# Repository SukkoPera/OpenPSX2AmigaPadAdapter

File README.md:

# OpenPSX2AmigaPadAdapter
OpenPSX2AmigaPadAdapter is an Open Hardware adapter that allows using a Sony PlayStation controller on Commodore computers, including the Commodore 64, Amiga and CD<sup>32</sup>.

## Summary
The Commodore Amiga CD<sup>32</sup> came with cumbersome and fragile controllers, most of which did not survive the challenge of time. While many third-party replacements have surfaced in the meantime, most of them are not as solid and comfortable as the ubiquitous Sony PlayStation controllers. These have more than enough buttons, are cheap and most people are familiar with them, as the same basic design has been around for nearly 25 years. This means they would be a very good replacement, if they just didn't use a different connector and communication protocol.

OpenPSX2AmigaPadAdapter is a simple [Arduino](https://www.arduino.cc)-based board that adapts the connector and translates the protocol, allowing the use of many PlayStation controllers on Commodore computers. It can either behave as a simple 1/2-button Atari-style joystick or as a full-fledged 7-button CD<sup>32</sup> gamepad. It can also appear as an Amiga mouse.

## Operating Modes
The adapter has two leds:
- LD1 lights up steadily when a supported controller is plugged in. It blinks when no controller - or an unsupported one - is connected.
- LD2 indicates the current operating mode, to be interpreted as follows.

### Two-Button Joystick Mode
When the adapter is powered on, it defaults to Atari-style Two-Button Mode, which is indicated by LD2 being off.

This mode has been throughly tested on several Amiga models, but it **should** work wherever an Atari-style joystick is supported, including the Commodore VIC-20, Commodore 16 (through an [adapter](https://github.com/SukkoPera/OpenC16JoyAdapter)), Commodore 64, etc. See [below](#computers-and-consoles) for a compatibility table.

While in this mode, the adapter supports different button mappings, which have been carefully designed and tailored to different game genres. The mappings can be switched by pressing <kbd>Select</kbd> in combination with other buttons. LD2 will blink quickly a few times to indicate what mapping has been activated.

#### Standard Mapping: <kbd>Select</kbd> + <kbd>&square;</kbd>
Standard Mapping is the simplest mapping possible: both the D-Pad and Left Analog work as direction buttons. <kbd>&square;</kbd> is <kbd>B1</kbd> and <kbd>&cross;</kbd> is <kbd>B2</kbd>. This is the default mapping as it should be usable just about in every game out there. It might not be the most natural these days, but it's the way the game was meant to be played by the developers, thus it should never fail you.

Note that very few games were originally made to take advantage of two buttons, as even fewer controllers had that many (!) those days. [Here is a list](http://eab.abime.net/showthread.php?t=57540) of Amiga games that somehow support two buttons, if it can be any useful.

LD2 will blink once when this mapping is activated.

#### Racing Mapping 1: <kbd>Select</kbd> + <kbd>&triangle;</kbd>
Racing Mapping 1 is useful for all those racing games that use <kbd>&uarr;</kbd> to accelerate and <kbd>&darr;</kbd> to brake. These have been mapped to <kbd>&square;</kbd> and <kbd>&cross;</kbd>, respectively, which should make them much more natural to play. When accelerating and braking at the same time, braking wins. Left Analog can be used to steer, but its vertical axis is ignored, to avoid accidental accelerating/braking. The D-Pad is fully functional and is handy when moving through menus. <kbd>B1</kbd> and <kbd>B2</kbd> can be found on <kbd>&triangle;</kbd> and <kbd>&cir;</kbd>.

This mode is probably best suited to games that do not involve shifting gears, as downshifting is usually performed through <kbd>&darr;</kbd> + <kbd>B1</kbd> which is pretty hard to achieve (<kbd>&triangle;</kbd> + <kbd>&cross;</kbd>).

LD2 will blink twice when this mapping is activated.

#### Racing Mapping 2: <kbd>Select</kbd> + <kbd>&cir;</kbd>
Racing Mapping 2 is an alternative mapping for racing games that was inspired by GTA V. It lets you use <kbd>R2</kbd> (or <kbd>R1</kbd>) to accelerate and <kbd>L2</kbd> (or <kbd>L1</kbd>) to brake (which means they map to <kbd>&uarr;</kbd> and <kbd>&darr;</kbd>, respectively). <kbd>B1</kbd> is mapped to its natural <kbd>&square;</kbd> position. Steering and the D-Pad work as in Racing Mode 1.

Accidentally, this control scheme was found out to be very comfortable with games that use <kbd>B1</kbd> to accelerate and <kbd>&uarr;</kbd> and <kbd>&darr;</kbd> to shift gears. Since <kbd>&darr;</kbd> is probably used for braking as well, it has also been mapped to <kbd>&cross;</kbd>, while <kbd>B2</kbd> has been moved to <kbd>&triangle;</kbd>.

LD2 will blink three times when this mapping is activated.

#### Platform Mapping: <kbd>Select</kbd> + <kbd>&cross;</kbd>
Platform Mapping is very similar to Standard Mapping, it just makes jumping way easier on a joypad and more natural to all the Mario players out there, by replicating <kbd>&uarr;</kbd> on <kbd>&cross;</kbd>. Consequently, <kbd>B2</kbd> has been moved to <kbd>&triangle;</kbd>.

LD2 will blink four times when this mapping is activated.

#### Custom Mappings: <kbd>Select</kbd> + <kbd>R1</kbd>/<kbd>R2</kbd>/<kbd>L1</kbd>/<kbd>L2</kbd>
What if the built-in mappings are not enough? OpenPSX2AmigaPadAdapter allows you to make your own! And you can have up to four different ones, which are stored internally so that they can be recalled at any time. By default they behave similarly to the Standard Mapping, but they can be customized so that any button produces either the press of a single button or even of a button combo!

The programming procedure is as follows:

1. Press and hold <kbd>Select</kbd>, then press and hold one of <kbd>R1</kbd>/<kbd>R2</kbd>/<kbd>L1</kbd>/<kbd>L2</kbd> until LD2 starts blinking, finally release both buttons. You are now in Programming Mode.
2. Press the button you want to configure. LD2 will flash quickly a few times.
3. Press and hold the single button or button combo you want to be assigned to the button you pressed before. At this stage the D-Pad directions have their obvious meaning, while <kbd>&square;</kbd> represents <kbd>B1</kbd> and <kbd>&cross;</kbd> represents <kbd>B2</kbd>. LD2 will again flash quickly a few times.
4. Release the button or combo you were holding.
5. Repeat steps 2-4 for every button you want to customize.
6. When you are done, press <kbd>Select</kbd> to store the mapping and leave Programming Mode. LD2 will stop blinking and you will be back to Two-Button Joystick Mode.

Note that a mapping you have just programmed is not activated automatically, so you will have to press <kbd>Select</kbd> and one of <kbd>R1</kbd>/<kbd>R2</kbd>/<kbd>L1</kbd>/<kbd>L2</kbd> (and release them quickly) to switch to it.

The Custom Mappings **cannot** be configured so that <kbd>&darr;</kbd> overrides <kbd>&uarr;</kbd> or so that the vertical axis of Left Analog is ignored, still they might be useful here and there. For instance, having <kbd>B1</kbd> + <kbd>&uarr;</kbd> on <kbd>&cross;</kbd> and <kbd>B1</kbd> + <kbd>&darr;</kbd> on <kbd>&triangle;</kbd> makes the Amiga version of *Golden Axe* much more playable.

#### Commodore 64 Mode
Button 2 on Commodore 64 usually behaves in the opposite way at the electrical level, with respect to the other buttons. So a tweak can be enabled to invert the behaviour of button 2, use it if you find that your game of choice always sees it pressed or if it triggers on release rather than on press.

Just hold <kbd>Select</kbd> and press <kbd>Start</kbd> briefly. LD2 will flash once when this tweak is enabled and twice when it is disabled.

### Mouse Mode
Whenever the right analog stick is moved, the adapter switches to Amiga Mouse Mode. In this mode, the right stick emulates the movements of a mouse. Movement speed is somewhat proportional to how far the stick is moved.

This mode can be useful as an emergency mouse, and it will be particularly handy if you have the adapter connected to port 1 of an Amiga computer and you need to use a mouse for short while (maybe to do some settings in a cracktro). Instead of unplugging the adapter, plugging in a mouse, and then the adapter again, you can take advantage of this feature.

Mouse mode is indicated by LD2 blinking. Press any direction on the D-Pad to go back to Joystick or CD32 Mode.

### CD<sup>32</sup> Controller Mode
When the adapter is connected to a CD<sup>32</sup> console, it will automatically switch into this mode, which will emulate all 7 buttons of the original CD<sup>32</sup> controller. LD2 will light up steadily.

By default, buttons are mapped as follows:
- <kbd>&square;</kbd>: Red
- <kbd>&cross;</kbd>: Blue
- <kbd>&cir;</kbd>: Yellow
- <kbd>&triangle;</kbd>: Green
- <kbd>L1</kbd>/<kbd>L2</kbd>/<kbd>L3</kbd>: L
- <kbd>R1</kbd>/<kbd>R2</kbd>/<kbd>R3</kbd>: R
- <kbd>Start</kbd>: Start/Pause

If you press <kbd>Select</kbd>, the 4 main buttons get "rotated":
- <kbd>&cross;</kbd>: Red
- <kbd>&cir;</kbd>: Blue
- <kbd>&triangle;</kbd>: Yellow
- <kbd>&square;</kbd>: Green

Both the D-Pad and Left Analog always work as direction buttons.

## Components and Assembly
The board is basically a customized Arduino Uno, this means it was designed to work with an ATmega328P microcontroller, but you can also use ATmega88/A/P/PA or ATmega168/P microcontrollers, as they are pin-compatible and slightly cheaper. The A/P/PA suffixes usually identify somewhat minor chip revisions, the board should work with all of them. If you can, use P or PA versions, which consume less power. Note that at the moment the firmware uses 99% of the flash space available on an ATmega88 and any possible future improvements and/or new features are likely to overflow that, so you'd better use an ATmega168 at least.

A noteworthy exception to this rule is the ATmega328P**B**, which is NOT 100% pin-compatible with the 328P. Nevertheless, it MIGHT just work as well. It might also destroy whatever you connect the adapter to, so do it **at your own risk**.

You are recommended to solder the microcontroller first. The TQFP-32 package is easier to solder than it looks, watch some videos on YouTube and develop your own technique. Just make sure to orient it correctly.

Solder the oscillator then. You can either use a through-hole crystal with its caps (these will depend on the crystal, but usually 18-22pF are a good bet) or a 3-pin resonator. Whichever you choose, it shall have a frequency of 16 MHz. If you choose the crystal, you might want to put some insulation tape under it to avoid it touching the pads for the resonator.

Solder all the remaining parts in the order you prefer, just keep the controller connectors last.

Note that the PlayStation controller is powered at 3.3V and the interface signals use the same voltage. Due to the particular circuit used for level shifting (the microcontroller works at 5V), the MOSFETs [should really be BSS138](https://electronics.stackexchange.com/questions/367052/replace-bss138-with-ao3400a-in-level-shifter-circuit).

The PlayStation controller connector can be found from many Chinese sellers as a spare part. Get one with 90° pins, otherwise the adapter will be pretty awkward to use. The pins will be pretty short, but you should manage to solder it in place. Make sure it sits level on the board, otherwise it might not fit in the [3D-printable case](#enclosure), which you are recommended to use in order to make the adapter more mechanically solid. In alternative, some hot glue behind the connector (where the pins are) seems to do the same job, but it won't look as pretty.

**Hint:** If you don't have the PCB, you can build a full adapter with an Arduino Uno/Nano/Whatever board. This is not supported though, so you are on your own, but all the information you need is in the schematics or in the firmware code :).

## Firmware
Before you can use the adapter, you will need to load some firmware (i.e.: an Arduino sketch) on it. This can be found under the [firmware](https://github.com/SukkoPera/OpenPSX2AmigaPadAdapter/tree/master/firmware) directory, along with instructions.

## Compatibility
### Computers and Consoles
|System                           |Compatible             |Notes                                                                                                                                                                                |
|---------------------------------|-----------------------|-------------------------------------------------------------------------------------------------------------------------------------------------------------------------------------|
|Commodore Amiga (All models)     |    |Tested on A500+ and A1200 (1.D3), it is expected to be compatible with all models in both 2- and 7-button Joystick modes and in Mouse mode.                                          |
|Commodore Amiga CD<sup>32</sup>  |    |Both 2- and 7-button Joystick modes and Mouse mode. Games not using `lowlevel.library` might be a bit of hit-and-miss, please report any misbehaviours.                              |
|Commodore CDTV                   ||**Not tested yet**, but expected to work in 2-button Joystick mode and Mouse mode through a connector adapter.                                                                       |
|Commodore 64                     |    |Tested in 2-button Joystick mode, but second button untested. Mouse mode might damage CIA chips though, be careful not to turn it on!                                                |
|Commodore 16                     ||**Not tested yet**, but expected to work in 2-button Joystick mode through [OpenC16JoyAdapter](https://github.com/SukkoPera/OpenC16JoyAdapter). C16 only supports Button 1 though.   |
|Commodore VIC-20                 ||**Not tested yet**, but expected to work in 2-button Joystick mode. Be careful with Mouse mode.                                                                                      |
|Sega Master System               |      |Would probably work in 2-button Joystick mode if power was routed from pin 5 on the SMS controller port to pin 7 of the adapter.                                                     |
|Sega Mega Drive/Genesis          |      |Would probably work as an SMS controller with the same mod as above. Some more pin rerouting AND a custom firmware could make it appear as a Mega Drive 6-button controller.         |
|MSX                              |      |Would probably work in 2-button Joystick mode by swapping a few pins on the controller port.                                                                                         |

### Controllers
The latest versions of the OpenPSX2AmigaPadAdapter firmware use [PsxNewLib](https://github.com/SukkoPera/PsxNewLib) to read the PlayStation controller. This makes it compatible with (almost) all controllers.

Please refer to the [PsxNewLib Compatibility List](https://github.com/SukkoPera/PsxNewLib#compatibility-list) for details.

## Current Consumption
Following are the results of some rough measurements:
- An ATmega88PA-based OpenPSX2AmigaPadAdapter with an original Sony Dual Shock/Dual Shock 2 controller connected draws about 20 mA.
- Consumption rises to 25 mA with the dongle of my EastVita wireless controller, when the controller is connected. It peaks to 35 mA while it is searching for the controller.
- Using an ATmega328P bumps all consumptions by 5 mA.

This means that the current absorbed by the adapter is "reasonable" and that it should be safe to use in all cases. It is well below the 100 mA maximum available from any Amiga controller ports, for instance.

## Enclosure
Three different 3D-printable enclosures are currently available for this board:
- The [first](https://github.com/SukkoPera/OpenPSX2AmigaPadAdapter/tree/master/enclosure) one was kindly contributed by Petros Kokotis and needs screws for assembly.
- A [second one](https://www.thingiverse.com/thing:4620027) was designed by Lemaru and uses a snap-in design. It also has holes for the LEDs.
- [Another one](https://github.com/SukkoPera/OpenPSX2AmigaPadAdapter/tree/master/enclosure/cd32) was made by Gary Ogden and is better suited for use with the CD<sup>32</sup>, as it has some kind of bottom support.

My gratitude goes to all the three guys for their great work and support!

### Releases
If you want to get this board produced, you are recommended to get [the latest release](https://github.com/SukkoPera/OpenPSX2AmigaPadAdapter/releases) rather than the current git version, as the latter might be under development and is not guaranteed to be working.

Every release is accompanied by its Bill Of Materials (BOM) file and any relevant notes about it, which you are recommended to read carefully.

## License
The OpenPSX2AmigaPadAdapter documentation, including the design itself, is copyright &copy; SukkoPera 2019-2020.

OpenPSX2AmigaPadAdapter is Open Hardware licensed under the [CERN OHL v. 1.2](http://ohwr.org/cernohl).

You may redistribute and modify this documentation under the terms of the CERN OHL v.1.2. This documentation is distributed *as is* and WITHOUT ANY EXPRESS OR IMPLIED WARRANTIES whatsoever with respect to its functionality, operability or use, including, without limitation, any implied warranties OF MERCHANTABILITY, SATISFACTORY QUALITY, FITNESS FOR A PARTICULAR PURPOSE or infringement. We expressly disclaim any liability whatsoever for any direct, indirect, consequential, incidental or special damages, including, without limitation, lost revenues, lost profits, losses resulting from business interruption or loss of data, regardless of the form of action or legal theory under which the liability may be asserted, even if advised of the possibility or likelihood of such damages.

A copy of the full license is included in file [LICENSE.pdf](LICENSE.pdf), please refer to it for applicable conditions. In order to properly deal with its terms, please see file [LICENSE_HOWTO.pdf](LICENSE_HOWTO.pdf).

The contact points for information about manufactured Products (see section 4.2) are listed in file [PRODUCT.md](PRODUCT.md).

Any modifications made by Licensees (see section 3.4.b) shall be recorded in file [CHANGES.md](CHANGES.md).

The Documentation Location of the original project is https://github.com/SukkoPera/OpenPSX2AmigaPadAdapter/.

## Support the Project
Since the project is open you are free to get the PCBs made by your preferred manufacturer, however in case you want to support the development, you can order them from PCBWay through this link:

You get my gratitude and cheap, professionally-made and good quality PCBs, I get some credit that will help with this and [other projects](https://www.pcbway.com/project/member/shareproject/?bmbid=41100). You won't even have to worry about the various PCB options, it's all pre-configured for you!

Also, if you still have to register to that site, [you can use this link](https://www.pcbway.com/setinvite.aspx?inviteid=41100) to get some bonus initial credit (and yield me some more).

Again, if you want to use another manufacturer, feel free to, don't feel obligated :). But then you can buy me a coffee if you want:

### Get Help
If you need help or have questions, you can join [the official Telegram group](https://t.me/joinchat/HUHdWBC9J9JnYIrvTYfZmg).

### Thanks
- Gerd Kautzmann for information about the [CD32 controller protocol](http://gerdkautzmann.de/cd32gamepad/cd32gamepad.html)
- CuriousInventor for informtation about the [PlayStation controller protocol](http://store.curiousinventor.com/guides/PS2)
- majinga/screwbreaker for testing and bugfixes
- Petros Kokotis, Lemaru and Gary Ogden for the 3D-printable enclosures
- Sarang Dumbre for the [3D model of the PlayStation connector](https://grabcad.com/library/ps-connector-female-1)

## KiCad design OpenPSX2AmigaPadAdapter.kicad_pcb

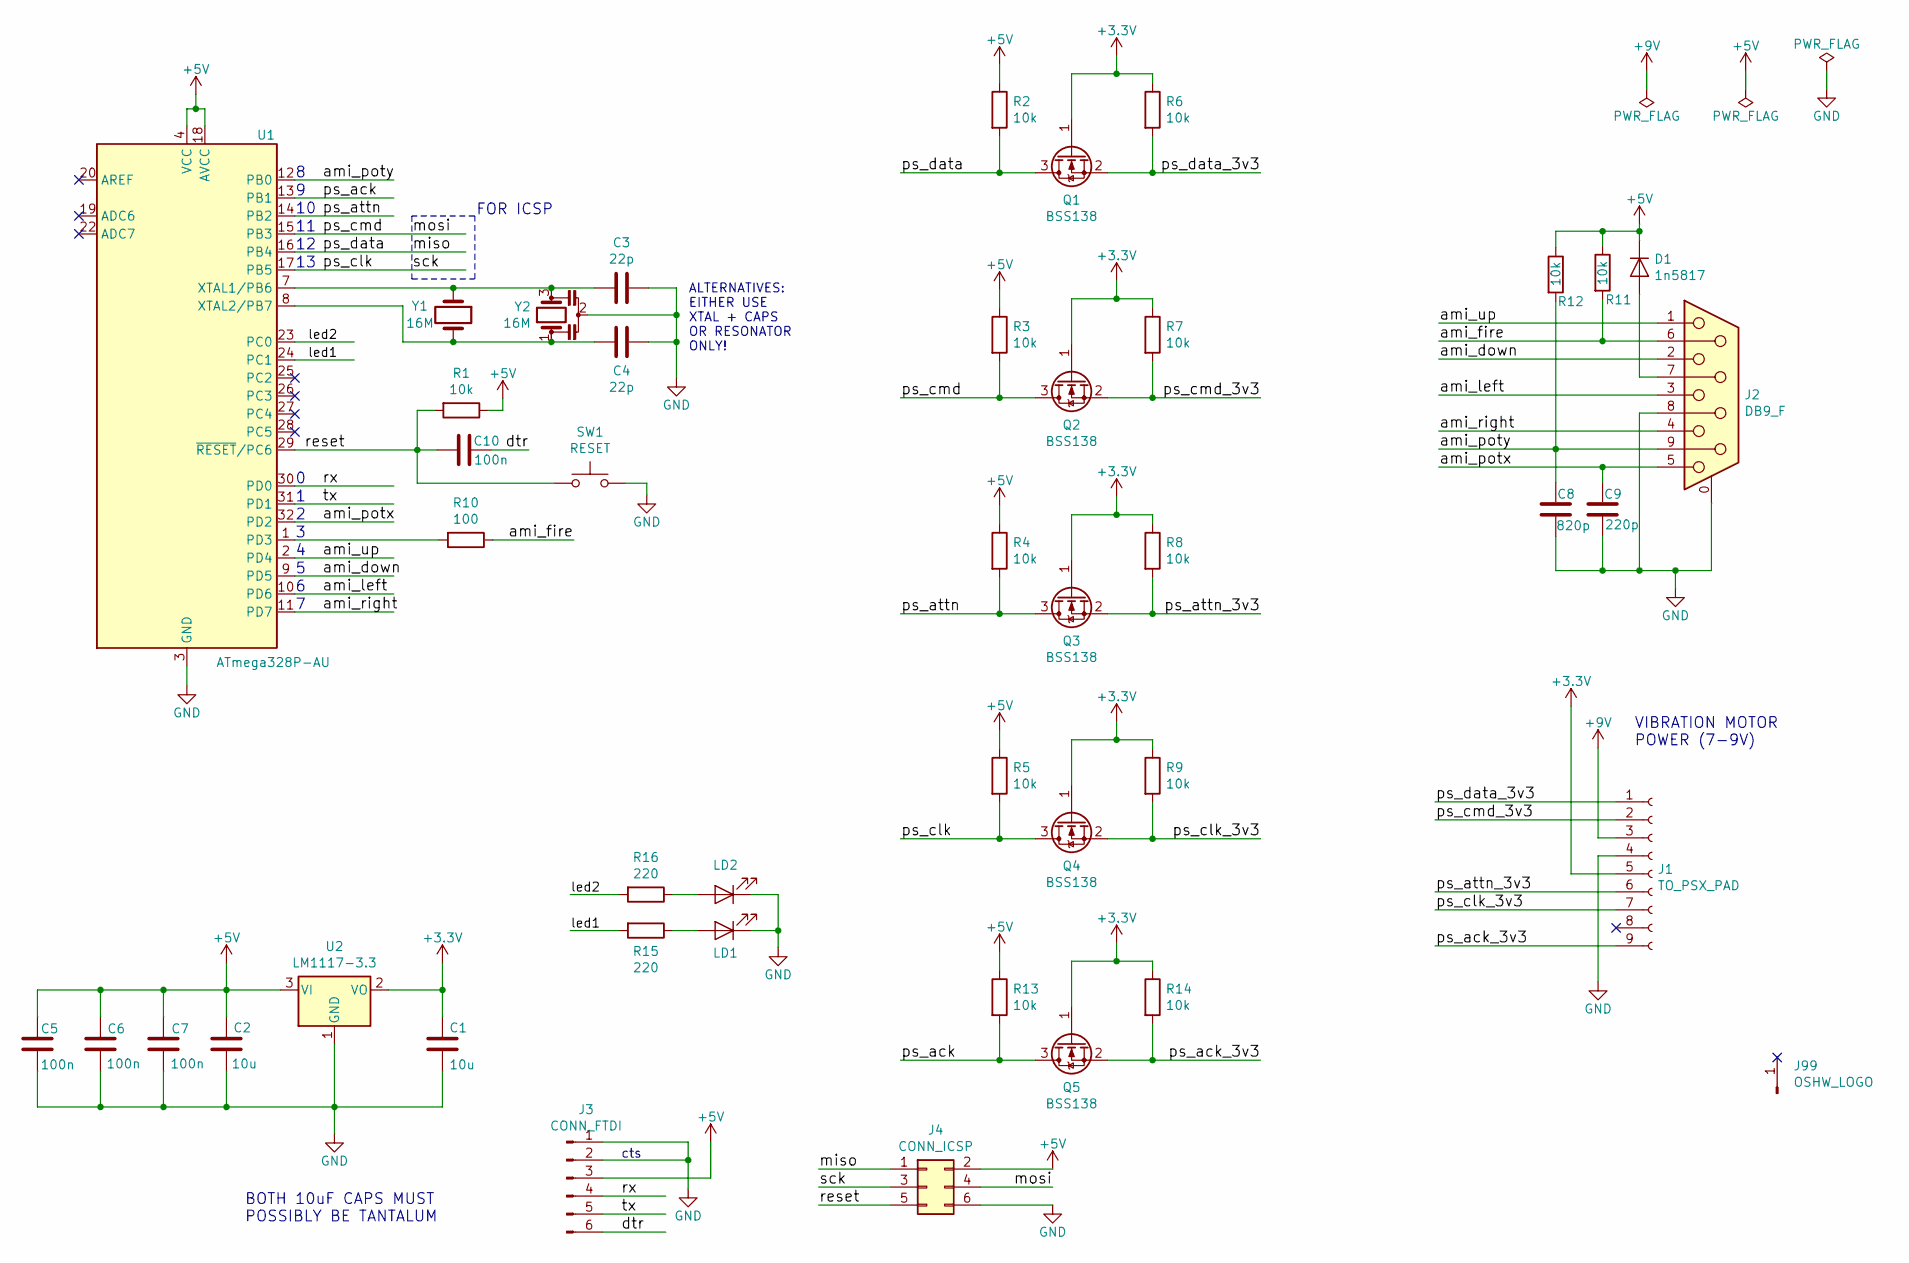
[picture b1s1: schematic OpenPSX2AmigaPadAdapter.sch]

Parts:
C1, C2: 10u; C_1206_3216Metric_Pad1.42x1.75mm_HandSolder
C3, C4: 22p; C_0805_2012Metric_Pad1.15x1.40mm_HandSolder
C5, C6, C7, C10: 100n; C_0805_2012Metric_Pad1.15x1.40mm_HandSolder
C8: 820p; C_0805_2012Metric_Pad1.15x1.40mm_HandSolder
C9: 220p; C_0805_2012Metric_Pad1.15x1.40mm_HandSolder
D1: 1n5817; D_SMA
J1: TO_PSX_PAD; PSX_Pad_Connector
J2: DB9_F; DB_9F
J3: CONN_FTDI; PinHeader_1x06_P2.54mm_Vertical
J4: CONN_ICSP; PinHeader_2x03_P2.54mm_Vertical
J99: OSHW_LOGO; OSHW-Logo_5.7x6mm_Copper
LD1, LD2: LED; LED_0805_2012Metric_Pad1.15x1.40mm_HandSolder
Q1, Q2, Q3, Q4, Q5: BSS138; SOT-23_Handsoldering
R1, R2, R3, R4, R5, R6, R7, R8, R9, R11, R12, R13, R14: 10k; R_0805_2012Metric_Pad1.15x1.40mm_HandSolder
R10: 100; R_0805_2012Metric_Pad1.15x1.40mm_HandSolder
R15, R16: 220; R_0805_2012Metric_Pad1.15x1.40mm_HandSolder
SW1: RESET
U1: ATmega328P-AU; TQFP-32_7x7mm_P0.8mm
U2: LM1117-3.3; SOT-223-3_TabPin2
Y1: 16M; Crystal_HC49-U_Vertical
Y2: 16M; Resonator_SMD_muRata_CSTxExxV

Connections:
+3V3: C1.2, J1.5, Q1.1 (G), Q2.1 (G), Q3.1 (G), Q4.1 (G), Q5.1 (G), R6.1, R7.1, R8.1, R9.1, R14.1, U2.2 (VO)
+5V: C2.2, C5.2, C6.2, C7.2, D1.1 (K), J3.3, J4.2, R1.1, R2.1, R3.1, R4.1, R5.1, R11.1, R12.1, R13.1, U1.4 (VCC), U1.6 (VCC), U1.18 (AVCC), U2.3 (VI)
/ami_down: J2.2, U1.9 (PD5)
/ami_fire: J2.6, R10.1, R11.2
/ami_left: J2.3, U1.10 (PD6)
/ami_potx: C9.1, J2.5, U1.32 (PD2)
/ami_poty: C8.1, J2.9, R12.2, U1.12 (PB0)
/ami_right: J2.4, U1.11 (PD7)
/ami_up: J2.1, U1.2 (PD4)
/dtr: C10.1, J3.6
/led1: R15.2, U1.24 (PC1)
/led2: R16.2, U1.23 (PC0)
/miso: J4.1, Q1.3 (D), R2.2, U1.16 (PB4)
/mosi: J4.4, Q2.3 (D), R3.2, U1.15 (PB3)
/ps_ack: Q5.3 (D), R13.2, U1.13 (PB1)
/ps_ack_3v3: J1.9, Q5.2 (S), R14.2
/ps_attn: Q3.3 (D), R4.2, U1.14 (PB2)
/ps_attn_3v3: J1.6, Q3.2 (S), R8.2
/ps_clk: J4.3, Q4.3 (D), R5.2, U1.17 (PB5)
/ps_clk_3v3: J1.7, Q4.2 (S), R9.2
/ps_cmd_3v3: J1.2, Q2.2 (S), R7.2
/ps_data_3v3: J1.1, Q1.2 (S), R6.2
/reset: C10.2, J4.5, R1.2, SW1.1, U1.29 (~RESET~/PC6)
/rx: J3.4, U1.30 (PD0)
/tx: J3.5, U1.31 (PD1)
GND: C1.1, C2.1, C3.1, C4.1, C5.1, C6.1, C7.1, C8.2, C9.2, J1.4, J2.0 (PAD), J2.8, J3.1, J3.2, J4.6, LD1.1 (K), LD2.1 (K), SW1.2, U1.3 (GND), U1.5 (GND), U1.21 (GND), U2.1 (GND), Y2.2
unnamed: C3.2, U1.7 (XTAL1/PB6), Y1.1, Y2.3
unnamed: C4.2, U1.8 (XTAL2/PB7), Y1.2, Y2.1
unnamed: D1.2 (A), J2.7
unnamed: LD1.2 (A), R15.1
unnamed: LD2.2 (A), R16.1
unnamed: R10.2, U1.1 (PD3)

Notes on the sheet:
VIBRATION MOTOR POWER (7-9V)
BOTH 10uF CAPS MUST POSSIBLY BE TANTALUM
FOR ICSP
ALTERNATIVES: EITHER USE XTAL + CAPS OR RESONATOR ONLY!
cts

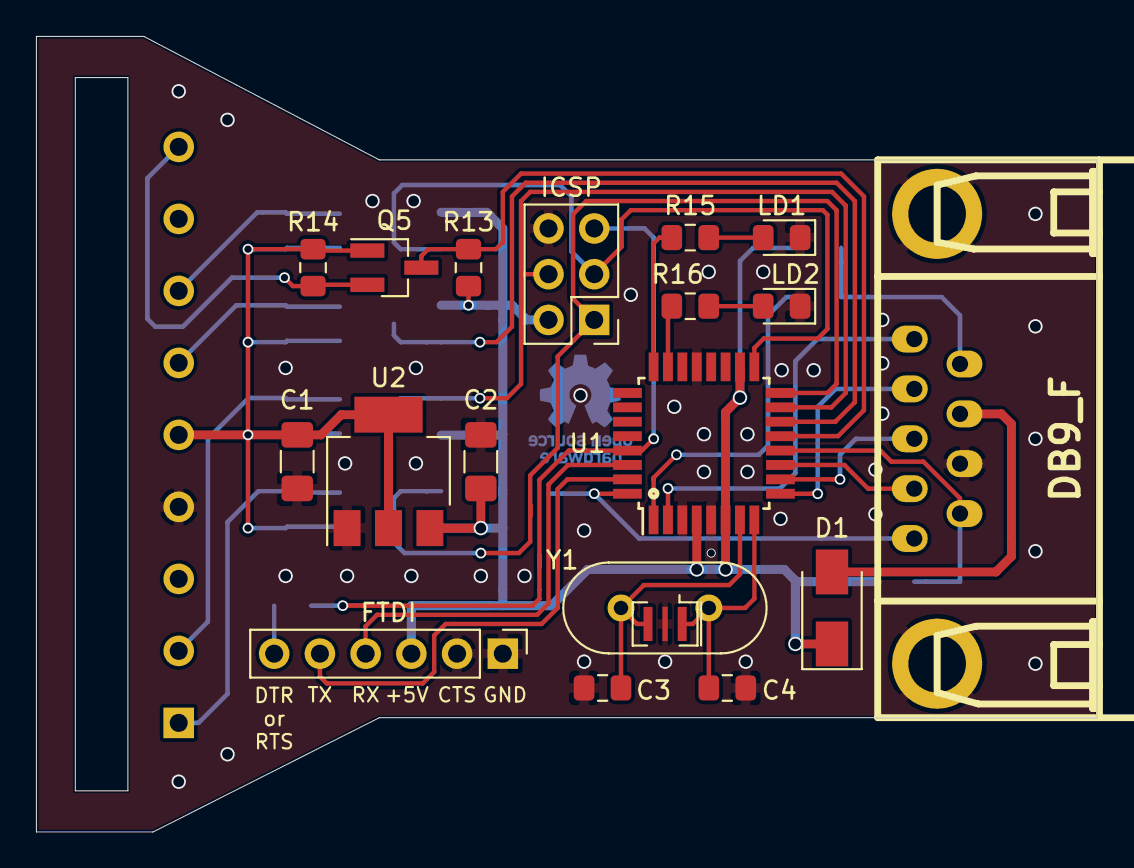
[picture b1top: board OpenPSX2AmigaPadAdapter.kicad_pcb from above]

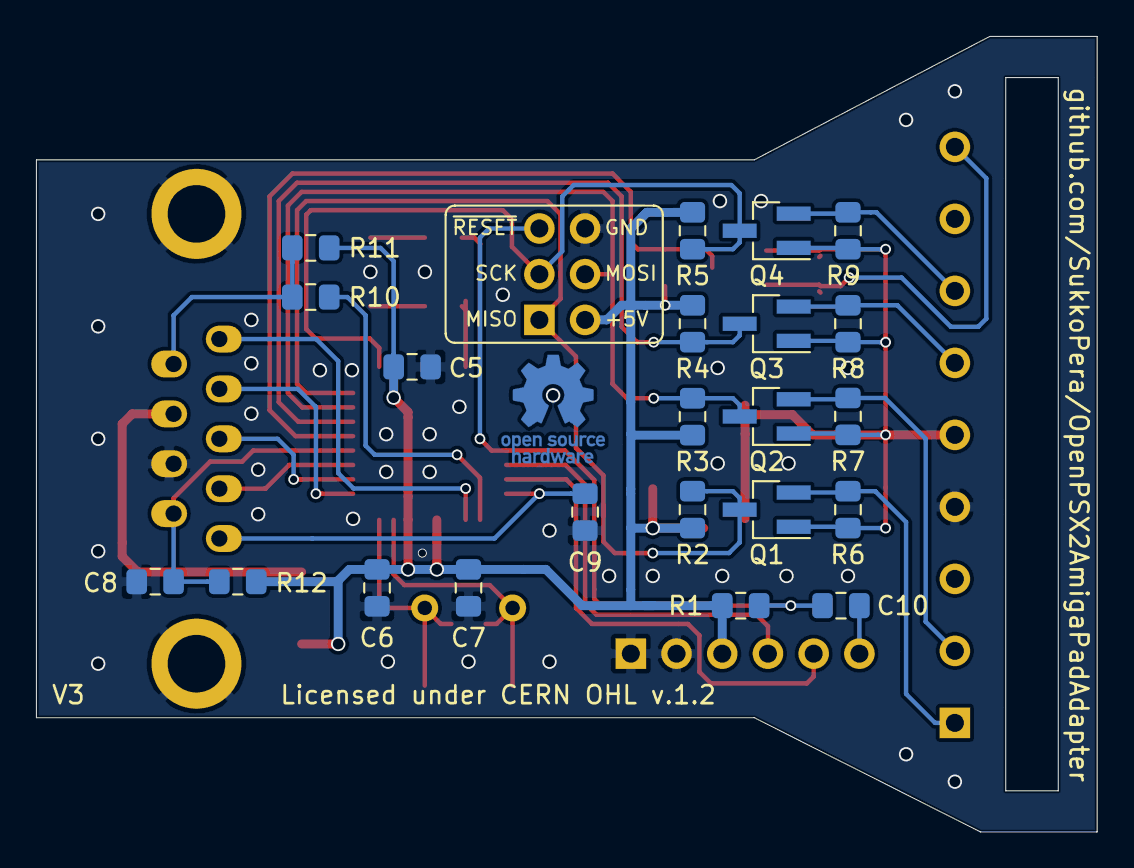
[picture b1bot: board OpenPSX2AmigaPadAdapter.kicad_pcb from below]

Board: 2 copper layers, 58.9 x 44.2 mm, 43 parts (23 on the bottom side), 32 nets.

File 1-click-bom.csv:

References,Qty,Description,Manufacturer,MPN,Manufacturer,MPN,Manufacturer,MPN,Manufacturer,MPN,Manufacturer,MPN,LCSC,Digikey,Mouser,RS,Newark,Farnell
J1,1,"1x09, 2.54mm pitch pin header",Molex,74099-0009,,,,,,,,,,23-0740990009-ND,538740990009,,,3036258
"C2, C1",2,10uF 1206,TDK,C3216JB1E106K160AB,AVX,TAJA106K016RNJ,Samsung Electro-Mechanics,CL31B106KAHNNNE,,,,,C7171,478-1655-1-ND,581TAJA106K016R,1354012,,1432339
"C7, C6, C5, C10",4,100nF 0805,Yageo,CC0805KRX7R9BB104,Murata,GCM21BR71H104KA37L,Murata,GRM21BR71H104KA01L,Guangdong Fenghua Advanced Tech,0805B104K500NT,,,C161260,311-1140-1-ND,603CC805KRX7R9BB104,6698842,,3019949
"C3, C4",2,22pF 0805,KEMET,C0805C220J5GAC,CCTC,TCC0805COG220J500BT,KEMET,C0805C220J5GACTU,,,,,C376875,399-1113-1-ND,80C0805C220J5GAC,2644258P,,1414678
"LD2, LD1",2,led 0805,Everlight,17-21/GHC-XS1T2M/3T,Lumex,SML-LXT0805GW-TR,Everlight,17-21SYGC/S530-E3/TR8,Rohm,SML-210VTT86,,,C63855,67-1553-6-ND,696SMLLXT0805GW,7007893,,2062259
"Q1, Q2, Q3, Q4",4,,MCC,BSS138-TP,,,,,,,,,C435876,BSS138-TPMSCT-ND,833BSS138TP,,,
"R1, R2, R3, R4, R5, R6, R7, R8, R9, R13, R12, R11",12,10k 0805,Vishay,CRCW080510K0FKEA,Panasonic,ERJ-6ENF1002V,Rohm,MCR10EZPJ103,Yageo,RC0805FR-0710KL,Guangdong Fenghua Advanced Tech,RS-05K103JT,C115295,311-10.0KCRCT-ND,603RC0805FR0710KL,1694499,,9237755
R10,1,100 ohm 0805,Vishay,CRCW0805100RFKEA,Panasonic,ERJ-6ENF1000V,Yageo,RC0805FR-07100RL,Guangdong Fenghua Advanced Tech,RS-05K101JT,,,C193990,311-100CRDKR-ND,603RC0805FR07100RL,7326034,,2459312
"R15, R14",2,220 ohm 0805,Yageo,AC0805JR-07220RL,LIZ Elec,CR0805F82200G,Panasonic,ERJ6ENF2200V,,,,,C413269,P220CCT-ND,667ERJ6ENF2200V,7326194,,2303479
U1,1,,,ATmega328P-AU,Microchip,ATMEGA328PB-AU,,,,,,,C132230,ATMEGA328PB-AU-ND,556ATMEGA328PBAU,1468928,,2523203
U2,1,LM1117-3.3 SOT-223-3,"Youtai Semiconductor Co., Ltd.",AMS1117-3.3,Texas Instruments,LM1117MPX-3.3/NOPB,,,,,,,C347222,LM1117MPX-3.3/NOPBDKR-ND,926LM1117MPX3.3NOPB,,,3122024
Y1 or Y2,1,Crystal THT HC-49 U 16Mhz,Murata,CSTNE16M0VH3C000R0,,,,,,,,,,490-17951-1-ND,81CSTNE16M0VH3C000R,,,
J3,1,"1x06, 2.54mm pitch, single row",Molex,90120-0126,,,,,,,,,,WM8076-ND,538901200126,6705039,,2313717
J4,1,"2x03, 2.54mm pitch",Molex,90131-0123,,,,,,,,,,WM50035-06-ND,538901310123,6703443,,2381222
J2,1,,TE Connectivity,3-1634584-2,,,,,,,,,C167327,A118456-ND,571316345842,,,8391360
SW1,1,tactile switch smt,Omron,B3S-1000,C&K Components,PTS840 GMP SMTR LFS,,,,,,,,CKN10513DKR-ND,611PTS840GMPSMTR,183701,,177807
D1,1,Diode SMA (DO-214AC) 1n5817,,1n5817,ON Semiconductor,1N5817RLG,,,,,,,C232461,1N5817RLGOSCT-ND,8631N5817RLG,6254972,,2440587
C8,1,820pF 0805,Walsin Technologies,0805B821K500CT,AVX,08055A821JAT2A,Vishay,VJ0805A821JXAAC,,,,,,478-1327-1-ND,77VJ0805A821JXAAC,1353221,,2896735
C9,1,220pF 0805,Fenghua Electronics,0402B221K500NT,Walsin Technologies,0805B221K500,AVX,08051A221JAT2A,KEMET,C0805C221J5GAC,,,,478-1286-1-ND,80C0805C221J5GAC,1351301,,498609

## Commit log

2019-01-01 Minor improvements
2019-06-30 Add cap for ATmega decoupling
2019-06-30 Port to KiCad 5
2019-06-30 Start work on PCB
2019-07-01 Add initial firmware Basically working in CD32 mode only
2019-07-01 This version seems to work pretty well With SysTest, at least. Needs some polishing anyway.
2019-07-02 Add mouse mode
2019-07-02 Begin working on PCB
2019-07-03 Ready?
2019-08-04 Ready for prototype
2019-08-04 Add dimensions
2019-09-10 Use pins as on PCB
2019-09-10 Fully implement button maps and general cleanup
2019-09-10 Avoid useless bit inversions
2019-09-10 Switch to... switch
2019-09-10 Remove register variable attempts These don't seem to be usable in Arduino
2019-09-10 Detach interrupt when switching back from CD32 mode
2019-09-11 Do not accelerate and brake at the same time
2019-09-11 Use better function/struct names
2019-09-11 Fix debug messages & do not crash when Amiga is reset
2019-09-11 Cleanup
2019-09-11 mapJoystick() -> handleJoystick()
2019-09-11 Ready for V2 Added RESET button and lotsa minor adjustments
2019-09-11 Fix dimension
2019-09-11 Use cross to brake when in Racing2, always set pin directions and some clean up
2019-09-12 Handle pad mode better
2019-09-12 Do not disable clock ISR too early
2019-09-12 Tidy up
2019-09-12 Do not set pin directions twice
2019-09-12 Avoid sampling interrupt catching button value being filled in
2019-09-13 Allow controller hotplugging & unplugging
2019-09-13 Add license
2019-09-13 Minor refinements
2019-09-14 Remove unused library
2019-09-14 Override spurious switch to mouse mode on controller disonnection
2019-09-16 Work in progress
2019-09-16 Programmable keys are a reality!
2019-09-16 Disable debug
2019-09-17 Blink when in programming mode
2019-09-19 Move attachInterrupt() to wrapper function
2019-09-19 Starts working with new state machine
2019-09-19 Use button names in debug messages and isolate led handling
2019-09-19 Rename led pin constant
2019-09-19 Add thanks
2019-09-19 Add NO_CONTROLLER state and cosmetic improvements
2019-09-19 Rationalize mouse mode and introduce the NO_CONTROLLER state
2019-09-20 Add footprint for SMD resonator
2019-09-20 Add pull-up resistors on DATA and ACK
2019-09-20 Cosmetic fixes
2019-09-25 Create Doxyfile
2019-09-25 Custom controller configurations are now saved and restored
2019-09-25 Rename enum value
2019-09-25 Allow 4 custom mappings
2019-09-26 Implement factory reset
2019-09-26 Compile fixes
2019-09-27 Some optimizations
2019-09-27 Remove wasMouse stuff
2019-09-28 Allow disabling factory reset (Saves flash for ATmega88)
2019-09-29 Disable debug by default
2019-10-01 Only allow programming of custom mappings
2019-10-01 Save some flash unifying button to index functions
2019-10-08 Slight optimization
2019-10-08 Another small optimization
2019-10-15 Add list of two-button games
2019-10-21 Switch back to joystick mode immediately after LOAD/SHIFT falling edge
2019-10-21 Remove pull-up on ACK. Add on B1/B2 outputs.
2019-10-21 Add capacitor on potx/y as per original CD32 controller
2019-10-21 Update PCB after changes to schematics
2019-10-23 Use fast I/O functions everywhere
2019-10-23 Add/Fix some super-optimizations
2019-10-23 Output buttons sooner
2019-10-23 Update state diagram and pin mapping
2019-10-23 Update pin mapping
2019-10-23 Fix CD32 mode led
2019-10-23 Minor optimizations
2019-10-23 Fix mouse mode
2019-10-23 Some cleanups
2019-10-23 Toggle pins in mouse mode
2019-10-23 Minor fixes
2019-10-25 Add plugin for Saleae Logic Analyzer
2019-10-25 Add submodule for Saleae Logic Analyzer plugin
2019-10-25 Readd submodule
2019-10-25 Do not use {at,de}tachInterrupt() with SUPER_OPTIMIZE
2019-10-28 Avoid switching pin directions during CD32 mode
2019-10-28 Add (optional) instrumentation calls These can be used to measure the time it takes us to react to clock pulses and how long ISRs last.
2019-10-28 Only poll controller every so often (Fixes mouse mode) Note that this required a lot of extra work.
2019-10-28 Make stateEnteredTime local again, and other optimizations Now we fit again on ATmega88's
2019-10-28 Remove cruft
2019-10-28 Keep state in GPIOR2, saves flash and makes us even faster
2019-10-29 Work on documentation
2019-10-29 Fix typo
2019-10-29 Ready for V2 PCB
2019-10-29 Ignore build directories
2019-10-29 Add README and bootloaders
2019-10-29 Fix title
2019-10-29 Fix heading
2019-10-29 Add README
2019-10-29 Do not switch from Mouse to CD32 mode
2019-10-30 Final PCB fixes for V2
2019-10-30 Add note about ArduinoISP
2019-10-30 Update state diagram
2019-10-30 Remove unused factory reset code
2019-10-30 Add C64-style 2nd button. Closes #4.
2019-10-30 Update bootloaders
2019-10-30 Add 328 and 328pb bootloaders
2019-11-03 Init joystick mode correctly after factory reset This is important because some (knockoff) controllers seem to report SELECT pressed at start. This made us start in factory reset mode for a moment, a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
2019-11-05 Fix typos
2019-11-07 Fix configuration clearing
2019-11-08 Add renders
2019-11-09 Add images
2019-11-09 Fix path
2019-11-09 Make maybe icon yellow
2019-11-09 Correct PCBway project link
2019-11-09 Crop renders
2019-11-09 Add 3D model of PSX connector
2019-11-09 Handle SELECT+START properly
2019-11-09 Add command for setting fuses of ATmega328PB
2019-11-09 Use preformatted text
2019-11-09 Use constant for TIMEOUT_PROGRAMMING_MODE
2019-11-09 Buttons -> PsxButtons
2019-11-10 Only map Square and Cross to B1/B2 with normal mapping
2019-11-10 Add state diagram image for people who don't have graphviz
2019-11-10 Make compatible with kitspace.org
2019-12-10 Use handsoldering footprints and fix FTDI connector
2019-12-23 Add alternative CD32 button mapping
2019-12-24 Follow CD32 mapping when in ST_JOYSTICK_TEMP
2019-12-24 Fix some comments
2020-01-02 Connect ACK signal and remove RESET button
2020-01-02 Fix component naming
2020-01-02 Add schematics
2020-02-19 Add Fusion 360 project of 3D-Printable enclosure
2020-03-25 Remove fp-info-cache
2020-03-26 Fix for latest changes in PsxNewLib
2020-03-26 Use PsxNewLib
2020-03-26 Use values from PsxNewLib headers
2020-03-26 Update docs
2020-03-26 Add info about the alternate CD32 button mapping
2020-03-26 Update copyright notice
2020-03-26 Update renders and board link
2020-04-23 Add flashing command for ATmega328PB
2020-10-02 added enclosure for cd32
2020-10-04 cleaned up and added no leg version
2020-11-07 Add info about all enclosures currently available
2020-11-07 Add note about LED holes
2021-04-25 Clear selectComboButton when it's no longer needed
2021-04-25 Improve logging of state transitions to/from CD32

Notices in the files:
OpenPSX2AmigaPadAdapter.kicad_pcb:
Licensed under CERN OHL v.1.2
